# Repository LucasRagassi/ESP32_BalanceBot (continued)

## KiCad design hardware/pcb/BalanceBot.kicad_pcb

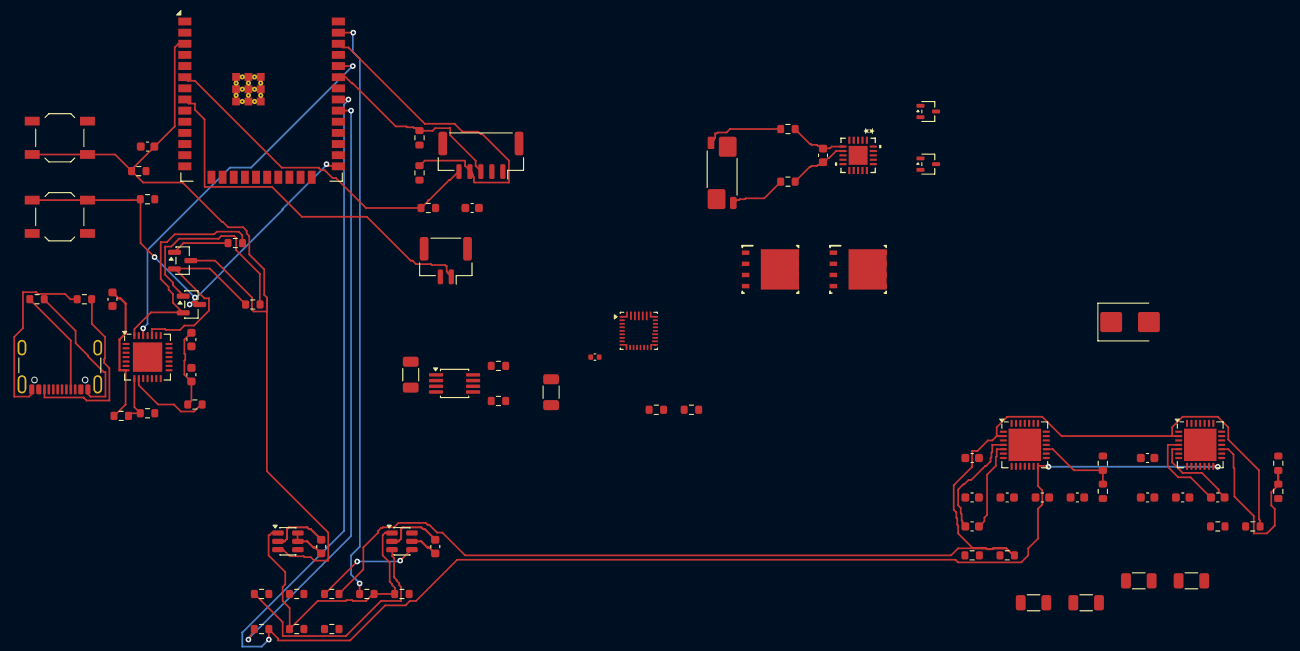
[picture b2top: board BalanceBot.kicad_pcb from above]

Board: 4 copper layers, 81 parts (0 on the bottom side), 65 nets.

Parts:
C1: 1uF; C_0603_1608Metric
C2: 10uF 25V; C_1206_3216Metric
C3: 22uF; C_1206_3216Metric
C4, C6, C29, C35, C39, C45, C49, C50, C51: 100nF; C_0603_1608Metric
C5: 4,7uF; C_0603_1608Metric
C34: 1nF 50V; C_0402_1005Metric
C36: 22uF; C_0603_1608Metric
C38, C42, C44, C48: 100nF 50V X7R; C_0603_1608Metric
C41, C47: 22nF 50V; C_0603_1608Metric
D1, D2: BAS40W,115; SOT-323_SC-70
D3: SMBJ10CA DNP; D_SMB
J1: USB_C_Receptacle_USB2.0_16P; USB_C_Receptacle_GCT_USB4105-xx-A_16P_TopMnt_Horizontal
J11: IMU_3V3_GH; JST_GH_SM05B-GHS-TB_1x05-1MP_P1.25mm_Horizontal
J14: QUAL UART TX; JST_GH_SM02B-GHS-TB_1x02-1MP_P1.25mm_Horizontal
Q1, Q2: MMBT3904; SOT-23
Q3, Q4: CSD18540Q5B; DNK0008A
R1, R2: 5,1 kΩ; R_0603_1608Metric
R3, R4, R9, R10: 10K; R_0603_1608Metric
R5: 22.1K; R_0603_1608Metric
R6: 47,5K; R_0603_1608Metric
R7: 499K; R_0603_1608Metric
R8: 1K; R_0603_1608Metric
R11: 160K; R_0603_1608Metric
R16: WSK2512R0100FEA; R_Shunt_Vishay_WSK2512_6332Metric_T1.19mm
R17, R18: 100R; R_0603_1608Metric
R29, R30, R35, R36: 0.47R 1% 0.5W; R_1206_3216Metric
R31, R32, R37, R38, R41, R42, R47, R48: 10k; R_0603_1608Metric
R33, R39: 15k 1%; R_0603_1608Metric
R34, R40: 10k 1%; R_0603_1608Metric
R43: 0R DNP; R_0603_1608Metric
R44: 4.7k; R_0603_1608Metric
R45: 47k; R_0603_1608Metric
R46: 1k; R_0603_1608Metric
R49, R50: 2.2k 1% DNP; R_0603_1608Metric
R51: 100k; R_0603_1608Metric
R52: 5.23k 1% DNP; R_0603_1608Metric
R53: 30.1k 1%; R_0603_1608Metric
SW1: RESET; SW_SPST_TL3342
SW2: BOOT; SW_SPST_TL3342
U1: ESP32-WROOM-32E
U2: TPS62160DGK; MSOP-8_3x3mm_P0.65mm
U3: CP2102N-Axx-xQFN28; QFN-28-1EP_5x5mm_P0.5mm_EP3.35x3.35mm
U4: BQ25798; Texas_RQM0029A_VQFN-29_4x4mm_P0.4mm
U5: BQ76905RGRR; VQFN20_RGR_TEX
U6, U7: TMC2209-LA; VQFN-28-1EP_5x5mm_P0.5mm_EP3.7x3.7mm
U8: 74LVC1G10; SOT-23-6
U9: TPS3808DBV; SOT-23-6

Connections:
+3V3: C3.1, C35.1, C36.1, C39.1, C45.1, C49.1, C50.1, C51.1, J11.1, R3.2, R4.2, R7.1, R32.1, R38.1, R48.1, R49.1, R50.1, U1.2, U2.6, U6.15, U7.9, U7.15, U8.5, U9.5, U9.6
/B+: U4.22, U4.23
/B-: R16.1, U5.11, U5.21
/BMS_BAT: D1.3, U5.17
/BMS_DRAIN_COMMON: Q3.5, Q3.6, Q3.7, Q3.8, Q3.9, Q4.5, Q4.6, Q4.7, Q4.8, Q4.9
/BMS_KN: R16.3, R17.1
/BMS_KP: R16.2, R18.1
/BMS_REGSRC: D2.3, U5.16
/BMS_SRN: C29.1, R17.2, U5.7
/BMS_SRP: C29.2, R18.2, U5.6
/CELL1_SENSE: U5.1, U5.2, U5.3, U5.4, U5.19, U5.20
/CHG_TS: R52.2, R53.1, U4.16
/CP2102_3V3: C4.2, C5.1, R8.1, U3.6
/CP2102_DTR: Q2.2, R9.2, U3.28
/CP2102_RTS: Q1.2, R10.1, U3.24
/ENN_LOGIC: R43.1, U8.4
/ESP32_EN: C1.2, Q1.3, R3.1, SW1.2, U1.3, U9.3
/FRAME_USED_TX: J14.1, U1.8
/GPIO0: Q2.3, R4.1, SW2.1, U1.25
/IMU_DRDY: J11.5, R51.1, U1.6
/IMU_OK: R41.1, U8.3
/IMU_SCL: J11.4, R50.2, U1.36
/IMU_SDA: J11.3, R49.2, U1.33
/M_ARM_GPIO: R44.1, U1.37
/M_ARM_OK: R44.2, R45.1, R47.1, U8.1, U9.1
/M_A_5VOUT: R33.1, U6.8
/M_A_BRA: R29.1, U6.23
/M_A_BRB: R30.1, U6.27
/M_A_CPI: C41.2, U6.5
/M_A_CPO: C41.1, U6.4
/M_A_DIR: U1.11, U6.19
/M_A_STEP: R31.1, U1.10, U6.16
/M_A_VCP: C42.1, U6.6
/M_A_VREF: R33.2, R34.1, U6.17
/M_B_5VOUT: R39.1, U7.8
/M_B_BRA: R35.1, U7.23
/M_B_BRB: R36.1, U7.27
/M_B_CPI: C47.2, U7.5
/M_B_CPO: C47.1, U7.4
/M_B_DIR: U1.13, U7.19
/M_B_STEP: R37.1, U1.12, U7.16
/M_B_VCP: C48.1, U7.6
/M_B_VREF: R39.2, R40.1, U7.17
/M_ENN: R32.2, R38.2, R43.2, U6.2, U7.2
/PWR_OK: R42.1, U8.6
/REGN: R52.1, U4.5
/RXD0/GPIO3: U1.34, U3.26
/SHUNT_OUT: Q4.1, Q4.2, Q4.3, R16.4
/SYS_PWR: C2.1, U2.2, U2.3, U4.25
/TMC_TX: R46.1, U1.30
/TMC_UART: R46.2, U1.31, U6.14, U7.14
/TXD0/GPIO1: U1.35, U3.25
/USBC_D+: J1.A6, J1.B6, U3.4
/USBC_D-: J1.A7, J1.B7, U3.5
/USB_5V: C6.2, J1.A4, J1.A9, J1.B4, J1.B9, R5.1, U3.7, U4.2, U4.3, U4.8, U4.9
/VM_MOTOR: C38.1, C42.2, C44.1, C48.2, D3.2, U6.22, U6.28, U7.22, U7.28
GND: C1.1, C2.2, C3.2, C4.1, C5.2, C6.1, C34.2, C35.2, C36.2, C38.2, C39.2, C44.2, C45.2, C49.2, C50.2, C51.2, D3.1, J1.A1, J1.A12, J1.B1, J1.B12, J11.2, J14.2, Q3.1, Q3.2, Q3.3, R1.2, R2.2, R6.2, R11.2, R29.2, R30.2, R31.2, R34.2, R35.2, R36.2, R37.2, R40.2, R41.2, R42.2, R45.2, R51.2, R53.2, SW1.1, SW2.2, U1.1, U1.15, U1.38, U1.39, U2.1, U2.4, U3.3, U3.29, U4.10, U4.11, U4.17, U4.27, U6.3, U6.7, U6.9, U6.10, U6.13, U6.18, U6.20, U6.25, U6.29, U7.3, U7.7, U7.10, U7.13, U7.18, U7.20, U7.25, U7.29, U8.2, U9.2
unnamed: J1.A5, R1.1
unnamed: J1.B5, R2.1
unnamed: Q1.1, R9.1
unnamed: Q2.1, R10.2
unnamed: R7.2, R11.1, U2.5
unnamed: R5.2, R6.1, U3.8
unnamed: R8.2, U3.9
unnamed: C34.1, U4.24

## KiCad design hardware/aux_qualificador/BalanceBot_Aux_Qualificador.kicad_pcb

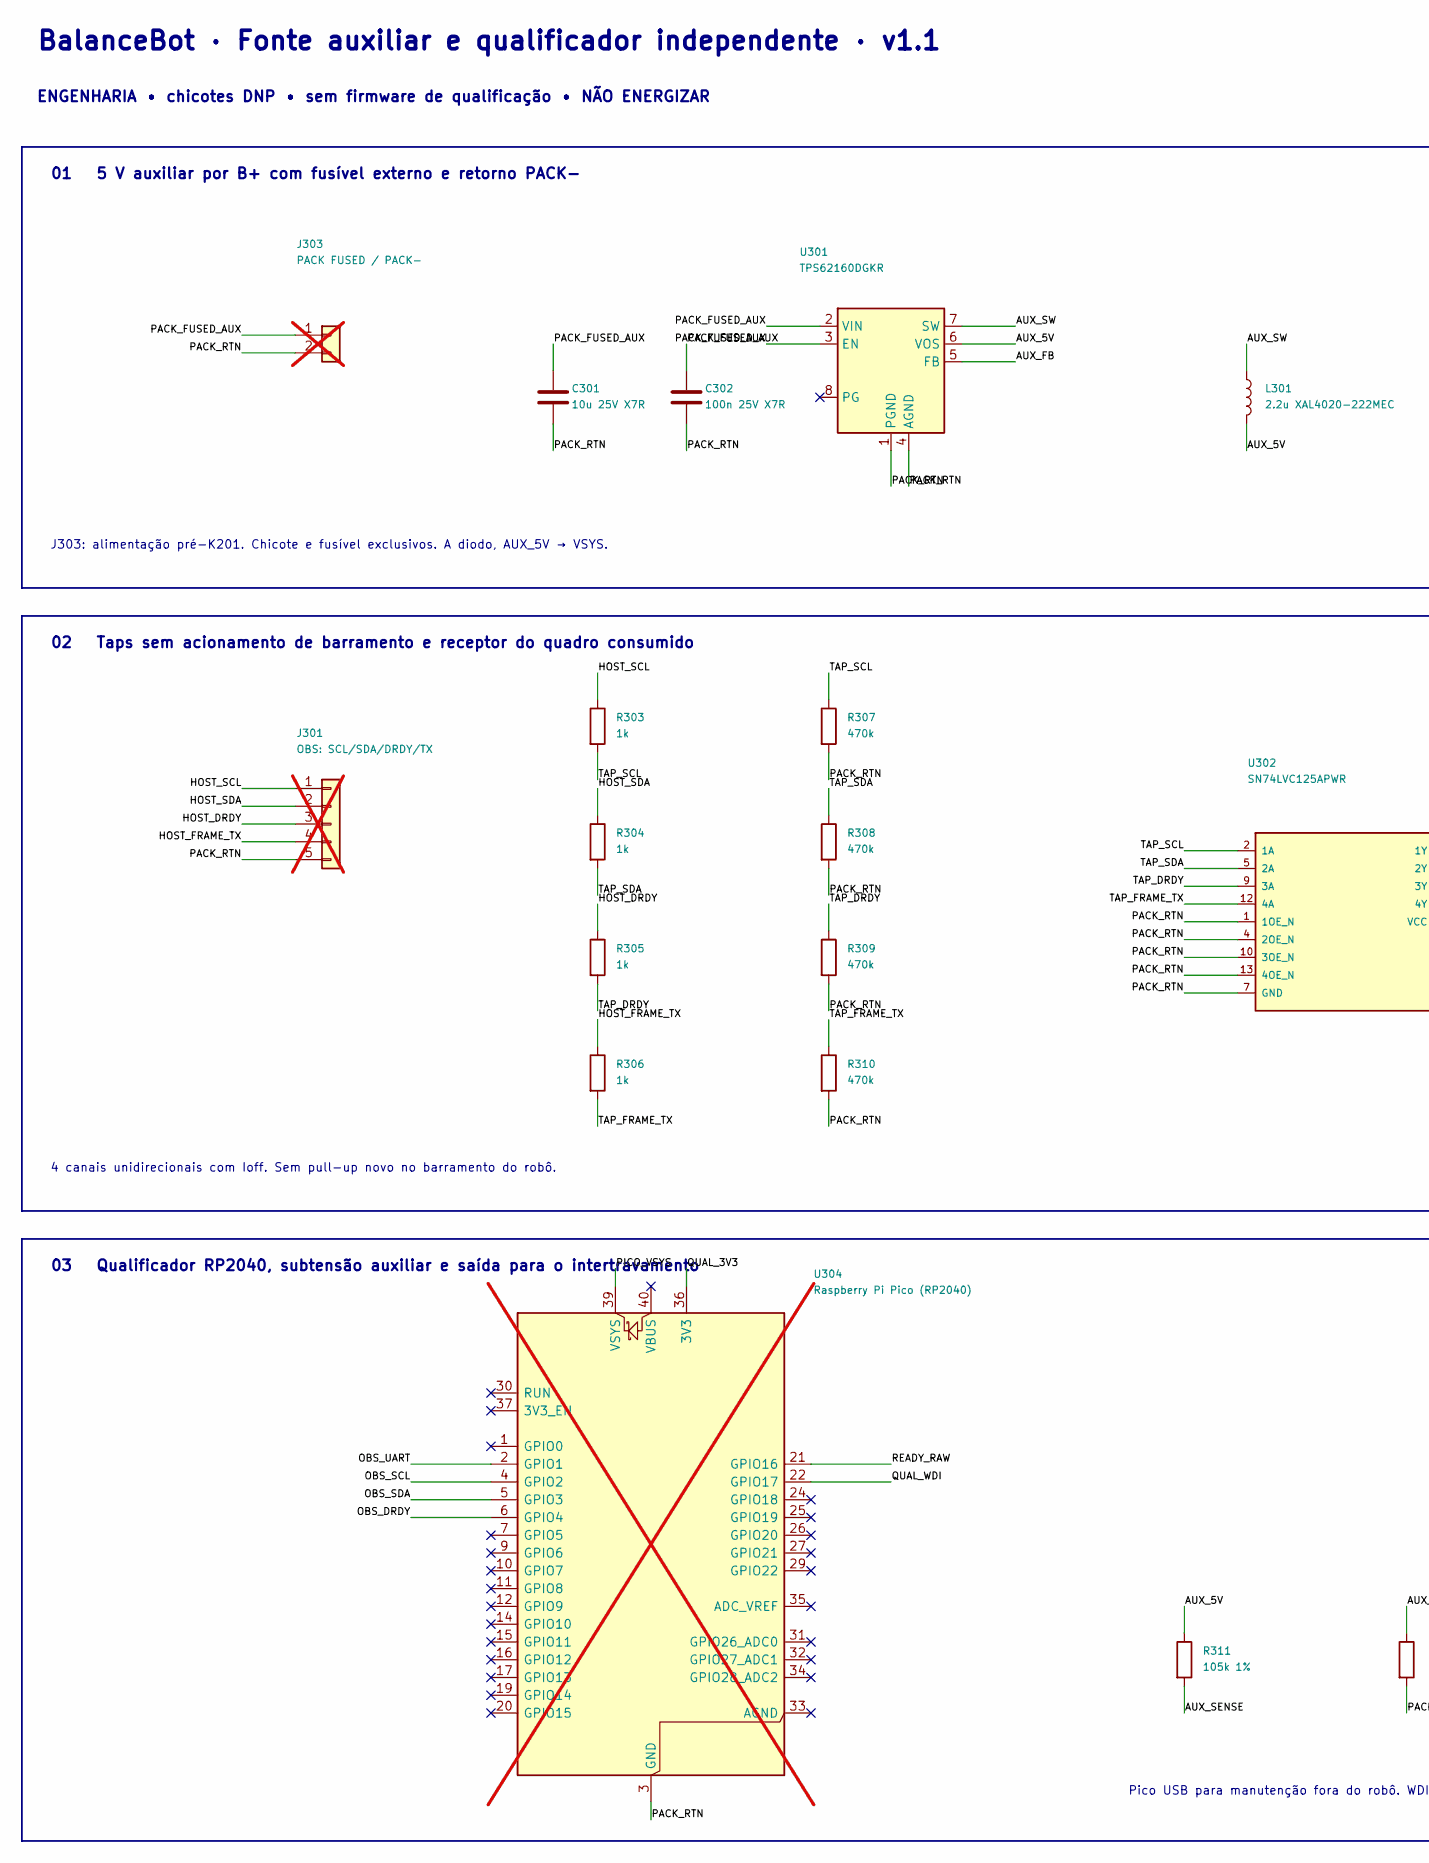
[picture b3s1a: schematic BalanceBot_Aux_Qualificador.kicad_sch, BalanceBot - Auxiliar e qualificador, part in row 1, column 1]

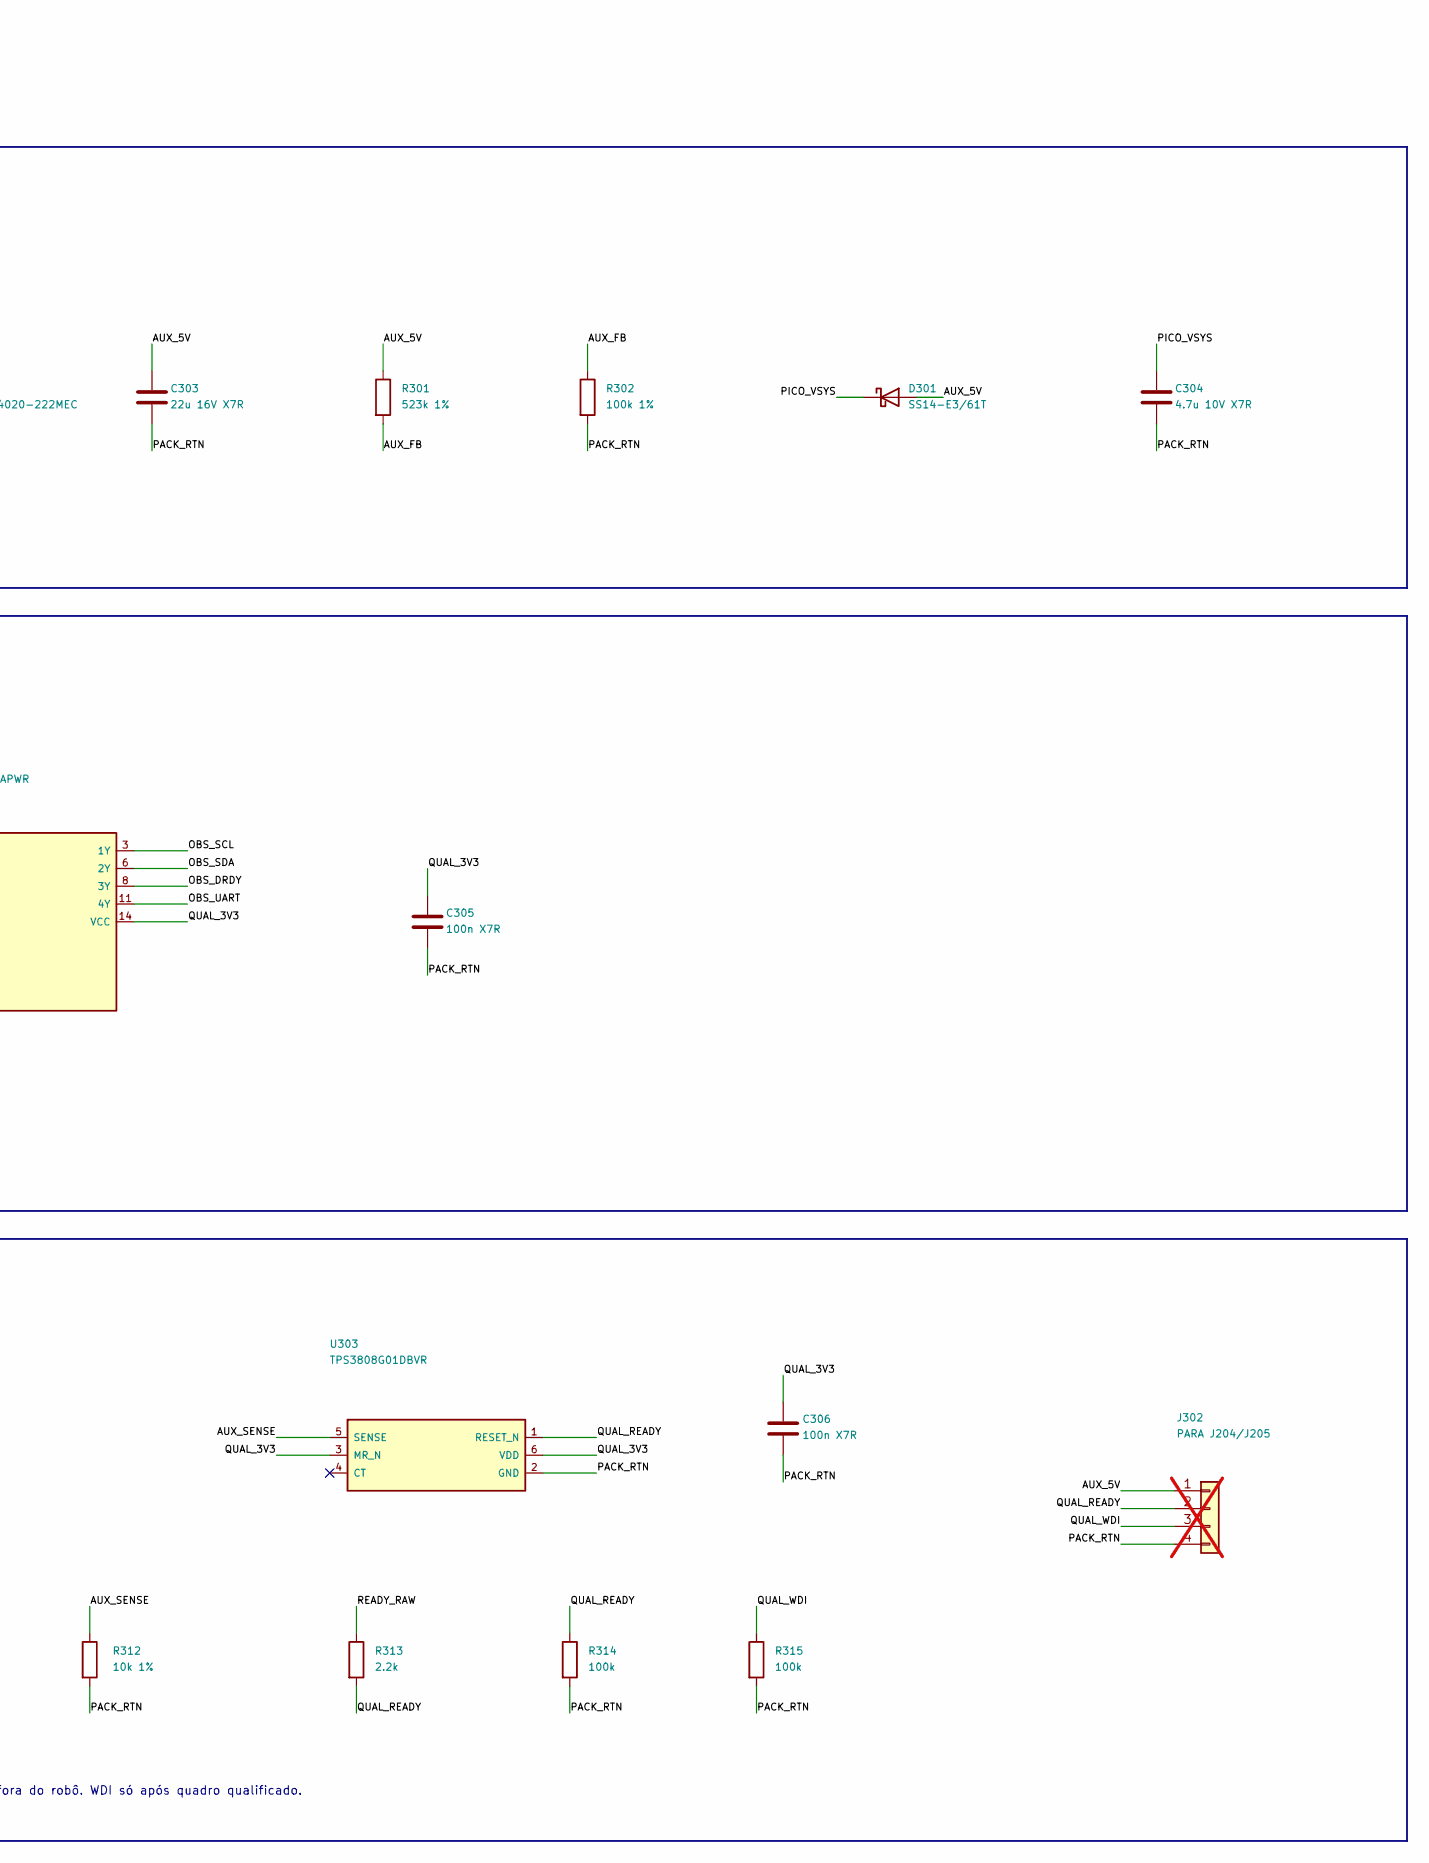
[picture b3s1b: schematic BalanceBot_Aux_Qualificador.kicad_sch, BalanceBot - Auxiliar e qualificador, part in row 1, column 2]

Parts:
C301: 10u 25V X7R; C_1206_3216Metric
C302: 100n 25V X7R; C_0603_1608Metric
C303: 22u 16V X7R; C_1206_3216Metric
C304: 4.7u 10V X7R; C_0805_2012Metric
C305, C306: 100n X7R; C_0603_1608Metric
D301: SS14-E3/61T; D_SMA
J301: OBS: SCL/SDA/DRDY/TX; JST_XH_B5B-XH-A_1x05_P2.50mm_Vertical; not fitted
J302: PARA J204/J205; JST_XH_B4B-XH-A_1x04_P2.50mm_Vertical; not fitted
J303: PACK FUSED / PACK-; JST_XH_B2B-XH-A_1x02_P2.50mm_Vertical; not fitted
L301: 2.2u XAL4020-222MEC; L_Coilcraft_XAL4020-XXX
R301: 523k 1%; R_0603_1608Metric
R302: 100k 1%; R_0603_1608Metric
R303, R304, R305, R306: 1k; R_0603_1608Metric
R307, R308, R309, R310: 470k; R_0603_1608Metric
R311: 105k 1%; R_0603_1608Metric
R312: 10k 1%; R_0603_1608Metric
R313: 2.2k; R_0603_1608Metric
R314, R315: 100k; R_0603_1608Metric
U301: TPS62160DGKR; MSOP-8_3x3mm_P0.65mm
U302: SN74LVC125APWR; TSSOP-14_4.4x5mm_P0.65mm
U303: TPS3808G01DBVR; SOT-23-6
U304: Raspberry Pi Pico (RP2040); RaspberryPi_Pico_Common_THT; not fitted

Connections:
/AUX_5V: C303.1, D301.2 (A), J302.1, L301.2, R301.1, R311.1, U301.6 (VOS)
/AUX_FB: R301.2, R302.1, U301.5 (FB)
/AUX_SENSE: R311.2, R312.1, U303.5 (SENSE)
/AUX_SW: L301.1, U301.7 (SW)
/HOST_DRDY: J301.3, R305.1
/HOST_FRAME_TX: J301.4, R306.1
/HOST_SCL: J301.1, R303.1
/HOST_SDA: J301.2, R304.1
/OBS_DRDY: U302.8 (3Y), U304.6 (GPIO4)
/OBS_SCL: U302.3 (1Y), U304.4 (GPIO2)
/OBS_SDA: U302.6 (2Y), U304.5 (GPIO3)
/OBS_UART: U302.11 (4Y), U304.2 (GPIO1)
/PACK_FUSED_AUX: C301.1, C302.1, J303.1, U301.2 (VIN), U301.3 (EN)
/PACK_RTN: C301.2, C302.2, C303.2, C304.2, C305.2, C306.2, J301.5, J302.4, J303.2, R302.2, R307.2, R308.2, R309.2, R310.2, R312.2, R314.2, R315.2, U301.1 (PGND), U301.4 (AGND), U302.1 (1OE_N), U302.4 (2OE_N), U302.7 (GND), U302.10 (3OE_N), U302.13 (4OE_N), U303.2 (GND), U304.3 (GND), U304.8 (GND), U304.13 (GND), U304.18 (GND), U304.23 (GND), U304.28 (GND), U304.38 (GND)
/PICO_VSYS: C304.1, D301.1 (K), U304.39 (VSYS)
/QUAL_3V3: C305.1, C306.1, U302.14 (VCC), U303.3 (MR_N), U303.6 (VDD), U304.36 (3V3)
/QUAL_READY: J302.2, R313.2, R314.1, U303.1 (RESET_N)
/QUAL_WDI: J302.3, R315.1, U304.22 (GPIO17)
/READY_RAW: R313.1, U304.21 (GPIO16)
/TAP_DRDY: R305.2, R309.1, U302.9 (3A)
/TAP_FRAME_TX: R306.2, R310.1, U302.12 (4A)
/TAP_SCL: R303.2, R307.1, U302.2 (1A)
/TAP_SDA: R304.2, R308.1, U302.5 (2A)

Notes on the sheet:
BalanceBot · Fonte auxiliar e qualificador independente · v1.1
ENGENHARIA • chicotes DNP • sem firmware de qualificação • NÃO ENERGIZAR
01 5 V auxiliar por B+ com fusível externo e retorno PACK−
J303: alimentação pré-K201. Chicote e fusível exclusivos. A diodo, AUX_5V → VSYS.
02 Taps sem acionamento de barramento e receptor do quadro consumido
4 canais unidirecionais com Ioff. Sem pull-up novo no barramento do robô.
03 Qualificador RP2040, subtensão auxiliar e saída para o intertravamento
Pico USB para manutenção fora do robô. WDI só após quadro qualificado.

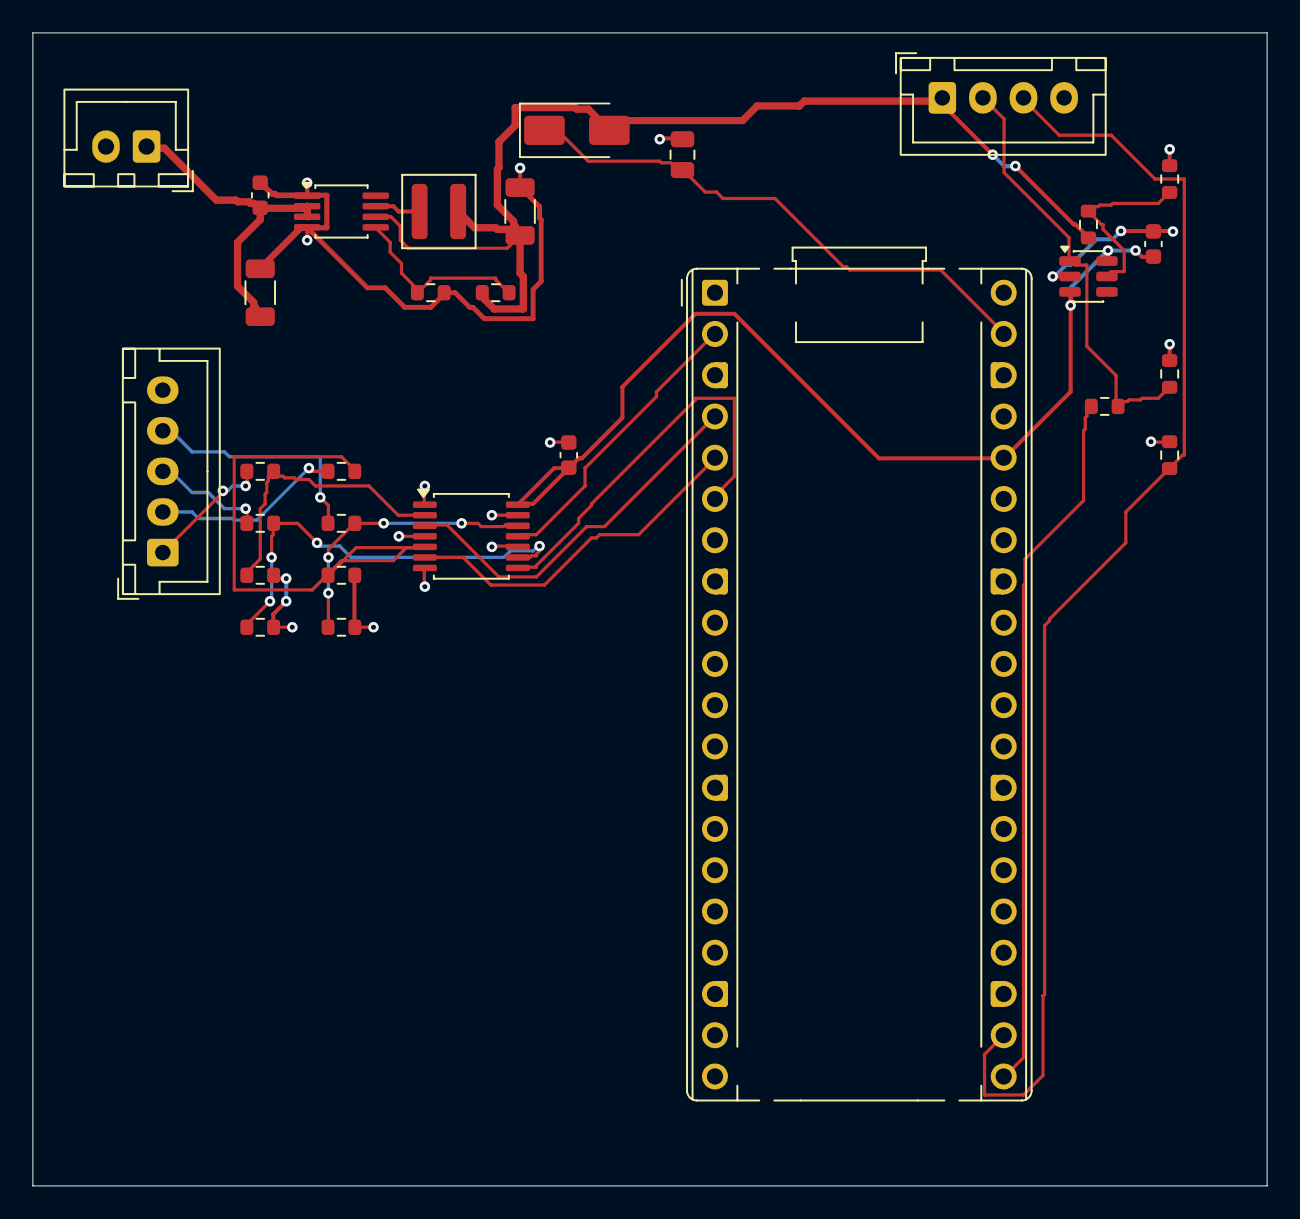
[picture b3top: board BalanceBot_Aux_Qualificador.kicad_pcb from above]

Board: 2 copper layers, 76.0 x 71.0 mm, 30 parts (0 on the bottom side), 23 nets.
